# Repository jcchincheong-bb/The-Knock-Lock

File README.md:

# Knock Lock

<!-- <div id="logo" align="center">
<figure>
  
</figure>
</div> -->

As children, many of us might have invented secret knocks that we used to identify ourselves to our friends or siblings. But, what if those special codes could actually unlock the door itself? As adults, how many times have you forgotten your keys and wished you could just knock in a certain way and the door would unlock for you? As such, the aim of The Knock Lock project is to design and assemble a system that unlocks a door by recognising a specific knocking pattern. As a proof of concept, the system will be designed as a small lock box with the hope of extending the idea to work on a full door in the future.

This project was done as part of the course 2314 Practical Electronics at HSRW. The full project report can be found [here](https://github.com/AbhinavK02/Knock-Lock/blob/main/ProjectReport.md).

<div align="center">
  <table border="0" style="width: 100%; border: none;">
    <tr>
      <td align="left" style="vertical-align: middle; width: auto; padding: 10px 0;">
        by: <a href="https://abhinavk02.github.io/">Abhinav Kothari</a> and <a href="https://jcchincheong-bb.github.io/">Justin Chin Cheong</a>
      </td>
      <td align="right" style="vertical-align: middle; width: 1%; white-space: nowrap; padding-left: 20px;">
        
      </td>
    </tr>
  </table>
  </figure>

</div>

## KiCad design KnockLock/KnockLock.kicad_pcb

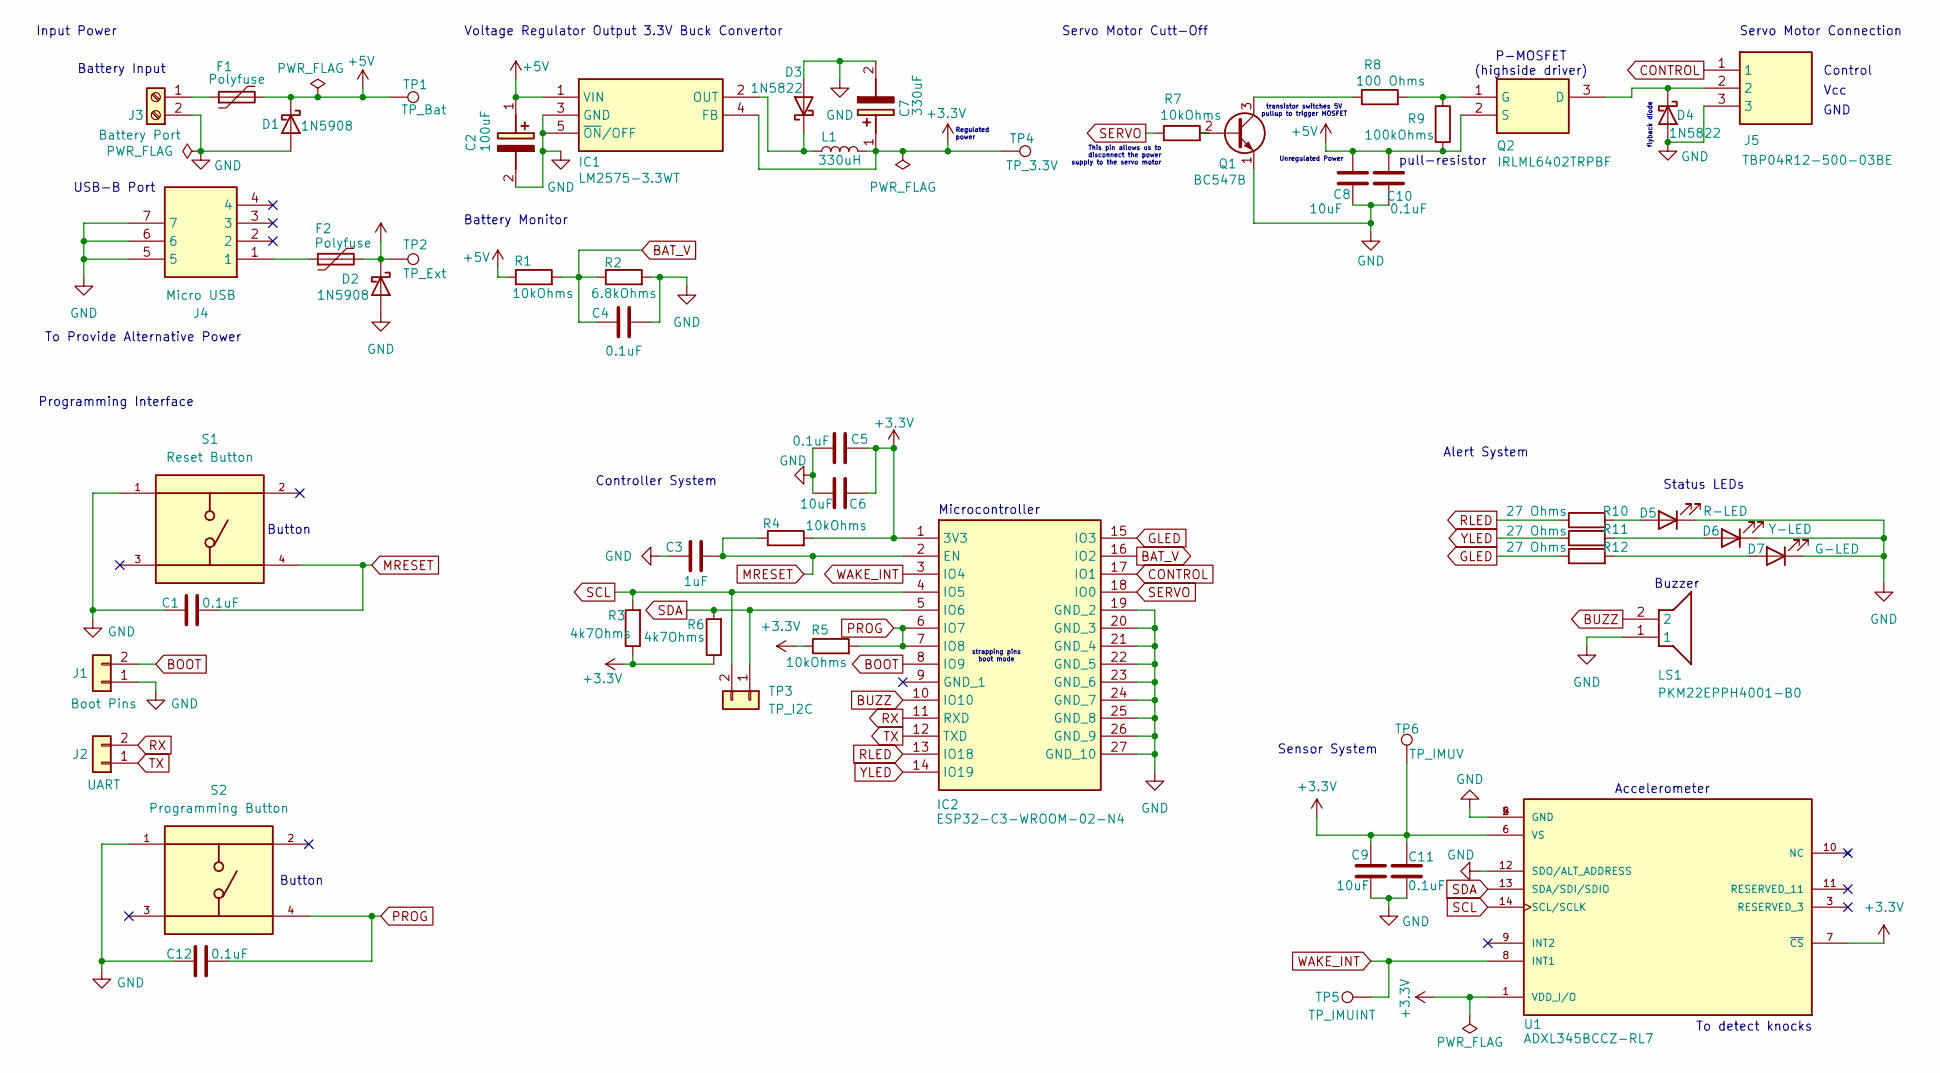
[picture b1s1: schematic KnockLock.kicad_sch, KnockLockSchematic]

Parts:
C1, C4, C5, C10, C11, C12: 0.1uF; C_0805_2012Metric_Pad1.18x1.45mm_HandSolder
C2: 100uF; CAPPRD250W55D630H1220; Mouser Part Number 667-EEU-FC1C101H
C3: 1uF; C_Radial_D4.0mm_H7.0mm_P1.50mm
C6, C8, C9: 10uF; C_Radial_D5.0mm_H11.0mm_P2.00mm
C7: 330uF; CAPPRD350W65D800H1300; Mouser Part Number 667-EEU-FR1E331
D1, D2: 1N5908; D_DO-201AD_P15.24mm_Horizontal
D3, D4: 1N5822; D_DO-201AD_P15.24mm_Horizontal
D5: R-LED; LED_D3.0mm
D6: Y-LED; LED_D3.0mm
D7: G-LED; LED_D3.0mm
F1, F2: Polyfuse; Fuse_BelFuse_0ZRE0012FF_L8.3mm_W3.8mm
IC1: LM2575-3.3WT; LM257533WT; Mouser Part Number 998-LM2575-3.3WT
IC2: ESP32-C3-WROOM-02-N4; ESP32C3WROOM02N4; Mouser Part Number 356-ESP32C3WROOM02N4
J1: Boot Pins; PinHeader_1x02_P2.54mm_Vertical
J2: UART; PinSocket_1x02_P2.54mm_Vertical
J3: Battery Port; TerminalBlock_bornier-2_P5.08mm
J4: Micro USB; USB3145301A; Mouser Part Number 640-USB3145-30-1-A
J5: TBP04R12-500-03BE; JST_EH_S3B-EH_1x03_P2.50mm_Horizontal; Mouser Part Number 179-TBP04R12-50003BE
L1: 330uH; L_Radial_D9.5mm_P5.00mm_Fastron_07HVP
LS1: PKM22EPPH4001-B0; PKM22EPPH4001B0; Mouser Part Number 81-PKM22EPPH4001-B0
Q1: BC547B; TO-92_HandSolder
Q2: IRLML6402TRPBF; SOT95P237X112-3N; Mouser Part Number 942-IRLML6402TRPBF
R1, R4, R5, R7: 10kOhms; R_1206_3216Metric_Pad1.30x1.75mm_HandSolder
R2: 6.8kOhms; R_1206_3216Metric_Pad1.30x1.75mm_HandSolder
R3, R6: 4k7Ohms; R_1206_3216Metric_Pad1.30x1.75mm_HandSolder
R8: 100 Ohms; R_1206_3216Metric_Pad1.30x1.75mm_HandSolder
R9: 100kOhms; R_1206_3216Metric_Pad1.30x1.75mm_HandSolder
R10, R11, R12: 27 Ohms; R_1206_3216Metric_Pad1.30x1.75mm_HandSolder
S1: Reset Button; SW_TS02-66-60-BK-260-LCR-D; PARTREV 1.0
S2: Programming Button; SW_TS02-66-60-BK-260-LCR-D; PARTREV 1.0
TP1: TP_Bat; TestPoint_Pad_D1.5mm
TP2: TP_Ext; TestPoint_Pad_D1.5mm
TP3: TP_I2C; PinSocket_1x02_P2.54mm_Vertical
TP4: TP_3.3V; TestPoint_Pad_D1.5mm
TP5: TP_IMUINT; PinSocket_1x01_P2.54mm_Vertical
TP6: TP_IMUV; TestPoint_Pad_D1.5mm
U1: ADXL345BCCZ-RL7; PQFN80P500X300X100-14N; PARTREV B

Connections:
+3.3V: C5.2, C6.2, C7.1 (+), C9.2, C11.2, IC1.4 (FB), IC2.1 (3V3), L1.2, R3.1, R4.2, R5.1, R6.1, TP4.1, TP6.1, U1.1 (VDD_I/O), U1.6 (VS), U1.7 (~CS)
+5V: C2.1 (+), C8.2, C10.2, D1.1 (K), D2.1 (K), F1.2, F2.2, IC1.1 (VIN), Q2.2 (S), R1.1, R9.2, TP1.1, TP2.1
BAT_V: C4.1, IC2.16 (IO2), R1.2, R2.1
BOOT: IC2.8 (IO9), J1.2
BUZZ: IC2.10 (IO10), LS1.2
CONTROL: IC2.17 (IO1), J5.1
GLED: IC2.15 (IO3), R12.1
GND: C1.1, C2.2 (-), C3.2, C4.2, C5.1, C6.1, C7.2 (-), C8.1, C9.1, C10.1, C11.1, C12.1, D1.2 (A), D2.2 (A), D3.2 (A), D4.2 (A), D5.1 (K), D6.1 (K), D7.1 (K), IC1.3 (GND), IC1.5 (~ON/OFF), IC2.19 (GND_2), IC2.20 (GND_3), IC2.21 (GND_4), IC2.22 (GND_5), IC2.23 (GND_6), IC2.24 (GND_7), IC2.25 (GND_8), IC2.26 (GND_9), IC2.27 (GND_10), J1.1, J3.2, J4.5, J4.6, J4.7, J5.3, LS1.1, Q1.1 (E), R2.2, S1.1, S2.1, U1.2 (GND), U1.4 (GND), U1.5 (GND), U1.12 (SDO/ALT_ADDRESS)
MRESET: C1.2, C3.1, IC2.2 (EN), R4.1, S1.4
unnamed: D3.1 (K), IC1.2 (OUT), L1.1
unnamed: D4.1 (K), J5.2, Q2.3 (D)
unnamed: D5.2 (A), R10.2
unnamed: D6.2 (A), R11.2
unnamed: D7.2 (A), R12.2
unnamed: F2.1, J4.1
unnamed: F1.1, J3.1
unnamed: Q1.2 (B), R7.2
unnamed: Q1.3 (C), R8.1
unnamed: Q2.1 (G), R8.2, R9.1
PROG: C12.2, IC2.6 (IO7), IC2.7 (IO8), R5.2, S2.4
RLED: IC2.13 (IO18), R10.1
RX: IC2.11 (RXD), J2.2
SCL: IC2.4 (IO5), R3.2, TP3.2, U1.14 (SCL/SCLK)
SDA: IC2.5 (IO6), R6.2, TP3.1, U1.13 (SDA/SDI/SDIO)
SERVO: IC2.18 (IO0), R7.1
TX: IC2.12 (TXD), J2.1
WAKE_INT: IC2.3 (IO4), TP5.1, U1.8 (INT1)
YLED: IC2.14 (IO19), R11.1

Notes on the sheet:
Voltage Regulator Output 3.3V Buck Convertor
Vcc
Battery Input
P-MOSFET (highside driver)
Controller System
To detect knocks
Control
Button
Programming Interface
flyback diode
strapping pins boot mode
Unregulated Power
Servo Motor Cutt-Off
Regulated power
Sensor System
GND
Buzzer
transistor switches 5V pullup to trigger MOSFET
Alert System
Servo Motor Connection
This pin allows us to disconnect the power supply to the servo motor
Input Power
Microcontroller
Accelerometer
Battery Monitor
Status LEDs
To Provide Alternative Power
USB-B Port
pull-resistor

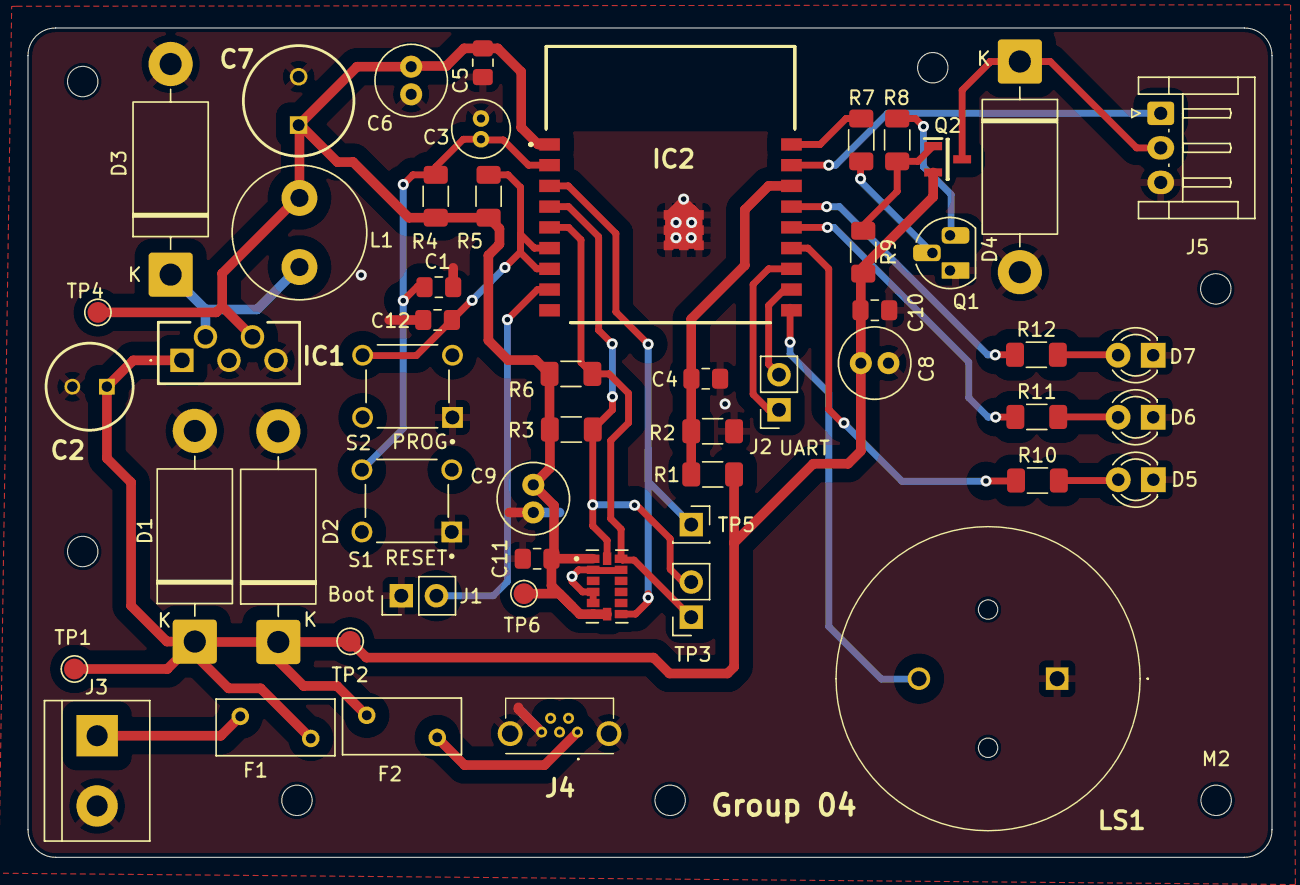
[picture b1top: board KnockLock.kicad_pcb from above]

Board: 2 copper layers, 90.0 x 60.0 mm, 55 parts (0 on the bottom side), 28 nets.

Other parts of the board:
M2, M2#2: MountingHole_2.2mm_M2_ISO7380

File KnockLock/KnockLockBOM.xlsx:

Item Number | Schematic Reference | Qty | Component | Part Number | Manufacturer | Vendor | Price Per Unit | Price
1 | U1 | 1 | Capacitive Accelerometer | ADXL345BCCZ-RL7 | Analog Devices | Mouser | 5.65 | 5.65 |  |  | Elect Cost | 26.61 | 15.05 | 11.56
2 | - | 1 | Servo Motor | SG90 | Soldered | HSRW | 5.07 | 5.07 |  |  | Mech Cost | 9.6999999999999993
3 | Q1 | 1 | Bipolar NPN Transistor | BC547B | CDIL | HSRW | 0.04 | 0.04 |  |  | PCB Cost | 7.24
4 | Q2 | 1 | P-channel MOSFET | IRLML6402TRPBF | Infineon Technologies | Mouser | 0.35 | 0.35 |  |  | Total Cost | 43.55
5 | IC2 | 1 | ESP32 Microcontroller | ESP32-C3-WROOM-02-N4 | Expressif Systems | Mouser | 3.12 | 3.12
6 | D5 | 1 | Red LED | DLE3MMR | Hottech | HSRW | 0.06 | 0.06
7 | D6 | 1 | Yellow LED | DLE3MMY | Hottech | HSRW | 0.06 | 0.06
8 | D7 | 1 | Green LED | DLE3MMG | Hottech | HSRW | 0.06 | 0.06
9 | LS1 | 1 | Buzzer | PKM22EPPH4001-B0 | Murata Electronics | Mouser | 0.48 | 0.48
10 | S1, S2 | 2 | Push Button | TS02-66-60-BK-260-LCR-D | Samesky | Mouser | 0.09 | 0.18
11 | IC1 | 1 | 3.3V Output Voltage Regulator | LM2575-3.3WT | Microchip Technology | Mouser | 1.48 | 1.48
12 | D1,D2 | 2 | TVS Diode | 1N5908 | STMicroelectronics | HSRW | 0.66 | 1.32
13 | D3,D4 | 2 | Schottky Diode | 1N5822 | MIC Electronics | HSRW | 0.15 | 0.3
14 | F1,F2 | 2 | Resettable Fuse | PFRA110 | Schurter | HSRW | 0.28000000000000003 | 0.56000000000000005
15 | - | 1 | Battery Holder | 2477 | Keystone Electronics | Mouser | 1.87 | 1.87
16 | - | 4 | AA Battery | - | - | HSRW | 0.3 | 1.2
17 | L1 | 1 | 330uH Inductor | RFC0810B-334KE | Coilcraft | Mouser | 1.26 | 1.26
18 | C1,C4,C5,C10,C11,C12 | 6 | 0.1uF Ceramic Capacitor SMT (0805) | B37873U5101S | EPCOS | HSRW | 0.11 | 0.66
19 | C2 | 1 | 100uF Electrolytic Capacitor | EEU-FC1C101H | Panasonic | HSRW | 0.14000000000000001 | 0.14000000000000001
20 | C3 | 1 | 1uF Electrolytic Capacitor | RA1/25-R | Jameco | HSRW | 0.02 | 0.02
21 | C6,C8,C9 | 3 | 10uF Electrolytic Capacitor | EEU-FR1H100 | Panasonic | HSRW | 0.11 | 0.33
22 | C7 | 1 | 330uF Electrolytic Capacitor | EEU-FR1E331 | Panasonic | HSRW | 0.26 | 0.26
23 | J1 | 1 | Male 2 Pin Header | - | - | HSRW | 0.08 | 0.08
24 | J2 | 1 | Female 2 Pin Header | - | - | HSRW | 0.1 | 0.1
25 | J3 | 1 | Male JST 2 Pin Header | - | - | HSRW | 0.1 | 0.1
26 | J4 | 1 | Micro USB B | USB3145-30-1-A | GCT | Mouser | 0.66 | 0.66
27 | J5 | 1 | Male JST 3 Pin Header | - | - | HSRW | 0.12 | 0.12
28 | R1,R4,R5,R7 | 4 | 10kOhms | RC1206FR-0710KL | YAGEO | HSRW | 0.09 | 0.36
29 | R2 | 1 | 6.8kOhms | RC1206FR-076K8L | YAGEO | HSRW | 0.09 | 0.09
30 | R3,R6 | 2 | 4k7Ohms | RC1206FR-074K7L | YAGEO | HSRW | 0.09 | 0.18
31 | R8 | 1 | 100 Ohms | RC1206FR-07100RL | YAGEO | HSRW | 0.09 | 0.09
32 | R9 | 1 | 100kOhms | RC1206FR-07100KL | YAGEO | HSRW | 0.09 | 0.09
33 | R10,R11,R12 | 3 | 27 Ohms | RC1206FR-0727RL | YAGEO | HSRW | 0.09 | 0.27
Item Number |  | Qty | Component | Price Per Unit | Price
35 |  | 7 | M2x6 Screw | 0.11 | 0.77
36 |  | 2 | M2x20 Screw | 0.14000000000000001 | 0.28000000000000003
37 |  | 1 | M3x15 Plastic Screw | 0.08 | 0.08
38 |  | 7 | M3 Plastic Washer | 0.01 | 7.0000000000000007E-2
39 |  | 1 | M3 Hex Nut | 7.0000000000000007E-2 | 7.0000000000000007E-2
40 |  | 1 | 3D Printed Housing | 8.43 | 8.43

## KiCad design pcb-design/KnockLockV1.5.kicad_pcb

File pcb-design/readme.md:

This is the folder where you save your pcb design with their related files. 

Please also submit a pdf / image version of your design

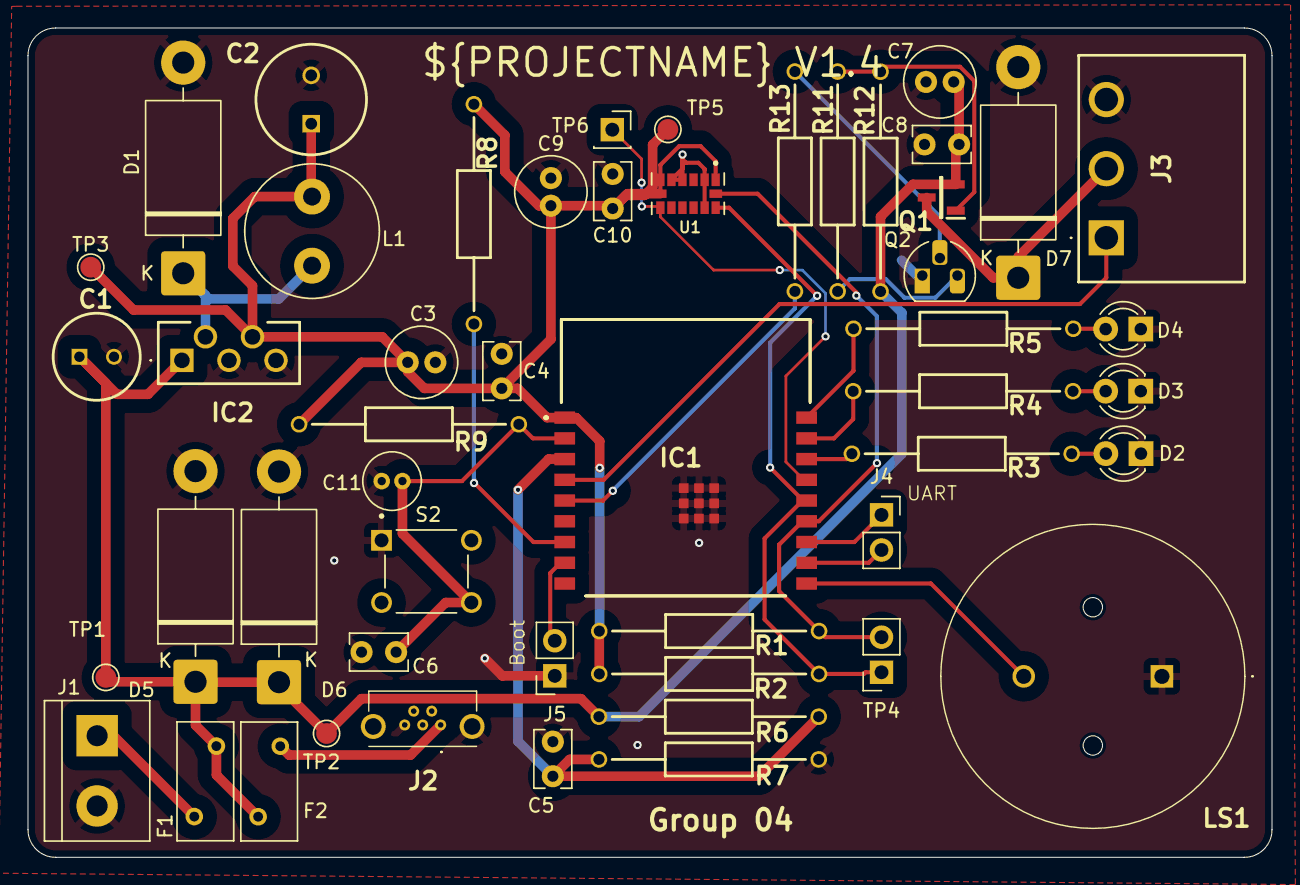
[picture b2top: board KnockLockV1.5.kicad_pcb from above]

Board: 2 copper layers, 90.0 x 60.0 mm, 51 parts (0 on the bottom side), 28 nets.

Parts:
C1: 100uF; CAPPRD250W55D630H1220
C2: 330uF; CAPPRD350W65D800H1300
C3, C7, C9: 10uF; C_Radial_D5.0mm_H11.0mm_P2.00mm
C4, C5, C6, C8, C10: 0.1uF; C_Rect_L4.0mm_W2.5mm_P2.50mm
C11: 1uF; C_Radial_D4.0mm_H7.0mm_P1.50mm
D1, D5, D6, D7: 1N5822; D_DO-201AD_P15.24mm_Horizontal
D2: R-LED; LED_D3.0mm
D3: Y-LED; LED_D3.0mm
D4: G-LED; LED_D3.0mm
F1, F2: Polyfuse; Fuse_BelFuse_0ZRE0012FF_L8.3mm_W3.8mm
IC1: ESP32-C3-WROOM-02-N4; ESP32C3WROOM02N4
IC2: LM2575-3.3WT; LM257533WT
J1: Screw_Terminal_01x02; TerminalBlock_bornier-2_P5.08mm
J2: USB3145-30-1-A; USB3145301A
J3: TBP04R12-500-03BE; TBP04R1250003BE
J4: UART; PinSocket_1x02_P2.54mm_Vertical
J5: Boot Pins; PinSocket_1x02_P2.54mm_Vertical
L1: 330uH; L_Radial_D9.5mm_P5.00mm_Fastron_07HVP
LS1: PKM22EPPH4001-B0; PKM22EPPH4001B0
Q1: IRLML6402TRPBF; SOT95P237X112-3N
Q2: BC547B; TO-92_HandSolder
R1, R2: 4k7Ohms; RESAD1590W60L630D240
R3, R4, R5: 27 Ohms; RESAD1590W60L630D240
R6, R8, R9, R13: 10kOhms; RESAD1590W60L630D240
R7: 6.8kOhms; RESAD1590W60L630D240
R11: 100 Ohms; RESAD1590W60L630D240
R12: 100kOhms; RESAD1590W60L630D240
S2: TS02-66-60-BK-260-LCR-D; SW_TS02-66-60-BK-260-LCR-D
TP1: TP_Bat; TestPoint_Pad_D1.5mm
TP2: TP_Ext; TestPoint_Pad_D1.5mm
TP3: TP_3.3V; TestPoint_Pad_D1.5mm
TP4: TP_I2C; PinSocket_1x02_P2.54mm_Vertical
TP5: TP_IMUV; TestPoint_Pad_D1.5mm
TP6: TP_IMUINT; PinSocket_1x01_P2.54mm_Vertical
U1: ADXL345BCCZ-RL7; PQFN80P500X300X100-14N

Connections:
+3.3V: C2.1 (+), C3.2, C4.2, C9.2, C10.2, IC1.1 (3V3), IC2.4 (FB), L1.2, R1.1, R2.1, R8.1, R9.2, TP3.1, TP5.1, U1.1 (VDD_I/O), U1.6 (VS), U1.7 (~CS)
+5V: C1.1 (+), C7.2, C8.2, D5.1 (K), D6.1 (K), F1.2, F2.2, IC2.1 (VIN), Q1.2 (S), R6.1, R12.2, TP1.1, TP2.1
BAT_V: C5.1, IC1.3 (IO4), R6.2, R7.1
BOOT: IC1.8 (IO9), J5.2
BUZZ: IC1.10 (IO10), LS1.2
CONTROL: IC1.4 (IO5), J3.1
GLED: IC1.18 (IO0), R5.1
GND: C1.2 (-), C2.2 (-), C3.1, C4.1, C5.2, C6.1, C7.1, C8.1, C9.1, C10.1, C11.2, D1.2 (A), D2.1 (K), D3.1 (K), D4.1 (K), D5.2 (A), D6.2 (A), D7.2 (A), IC1.19 (GND_2), IC1.20 (GND_3), IC1.21 (GND_4), IC1.22 (GND_5), IC1.23 (GND_6), IC1.24 (GND_7), IC1.25 (GND_8), IC1.26 (GND_9), IC1.27 (GND_10), IC2.3 (GND), IC2.5 (~ON/OFF), J1.2, J2.5, J2.6, J2.7, J3.3, J5.1, LS1.1, Q2.1 (E), R7.2, S2.1, U1.2 (GND), U1.4 (GND), U1.5 (GND), U1.12 (SDO/ALT_ADDRESS)
MRESET: C6.2, C11.1, IC1.2 (EN), R9.1, S2.4
unnamed: D1.1 (K), IC2.2 (OUT), L1.1
unnamed: D2.2 (A), R3.2
unnamed: D3.2 (A), R4.2
unnamed: D4.2 (A), R5.2
unnamed: D7.1 (K), J3.2, Q1.3 (D)
unnamed: F2.1, J2.1
unnamed: IC1.7 (IO8), R8.2
unnamed: F1.1, J1.1
unnamed: Q1.1 (G), R11.2, R12.1
unnamed: Q2.2 (B), R13.2
unnamed: Q2.3 (C), R11.1
RLED: IC1.16 (IO2), R3.1
RX: IC1.11 (RXD), J4.2
SCL: IC1.13 (IO18), R1.2, TP4.2, U1.14 (SCL/SCLK)
SDA: IC1.14 (IO19), R2.2, TP4.1, U1.13 (SDA/SDI/SDIO)
SERVO: IC1.5 (IO6), R13.1
TX: IC1.12 (TXD), J4.1
WAKE_INT: IC1.15 (IO3), TP6.1, U1.8 (INT1)
YLED: IC1.17 (IO1), R4.1

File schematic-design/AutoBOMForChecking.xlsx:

Reference | Qty | Value | DNP | Exclude from BOM | Exclude from Board | Footprint | Datasheet | Source | In Partslist
C1 | 1 | 100uF |  |  |  | SamacSys_Parts:CAPPRD250W55D630H1220 | http://industrial.panasonic.com/cdbs/www-data/pdf/RDF0000/AB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
C2 | 1 | 330uF |  |  |  | SamacSys_Parts:CAPPRD350W65D800H1300 | http://industrial.panasonic.com/cdbs/www-data/pdf/RDF0000/AB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
C3,C7,C9 | 3 | 10uF |  |  |  | Capacitor_THT:C_Radial_D5.0mm_H11.0mm_P2.00mm | ~
C4,C5,C6,C8,C10 | 5 | 0.1uF |  |  |  | Capacitor_THT:C_Rect_L4.0mm_W2.5mm_P2.50mm | ~ | Mouser | Y
C11 | 1 | 1uF |  |  |  | Capacitor_THT:C_Radial_D4.0mm_H7.0mm_P1.50mm | ~
D1,D5,D6,D7 | 4 | 1N5822 |  |  |  | Diode_THT:D_DO-201AD_P15.24mm_Horizontal | http://www.vishay.com/docs/88525/1n5817.pdf,http://www.vishay.com/docs/88526/1n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 | Reichelt | Y
D2 | 1 | R-LED |  |  |  | LED_THT:LED_D3.0mm | ~ | HSRW | Y
D3 | 1 | Y-LED |  |  |  | LED_THT:LED_D3.0mm | ~ | HSRW | Y
D4 | 1 | G-LED |  |  |  | LED_THT:LED_D3.0mm | ~ | HSRW | Y
F1,F2 | 2 | Polyfuse |  |  |  | Fuse:Fuse_BelFuse_0ZRE0012FF_L8.3mm_W3.8mm | ~ | HSRW | Y
IC1 | 1 | ESP32-C3-WROOM-02-N4 |  |  |  | SamacSys_Parts:ESP32C3WROOM02N4 | https://www.mouser.ch/datasheet/2/891/Espressif_ESP32_C3_WRO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
IC2 | 1 | LM2575-3.3WT |  |  |  | SamacSys_Parts:LM257533WT | https://ww1.microchip.com/downloads/en/DeviceDoc/lm2575.pdf | Mouser | Y
J1 | 1 | Screw_Terminal_01x02 |  |  |  | TerminalBlock:TerminalBlock_bornier-2_P5.08mm | ~
J2 | 1 | USB3145-30-1-A |  |  |  | SamacSys_Parts:USB3145301A | https://gct.co/connector/usb3145 | Mouser | Y
J3 | 1 | TBP04R12-500-03BE |  |  |  | SamacSys_Parts:TBP04R1250003BE | https://www.sameskydevices.com/product/resource/tbp04r12-500.pdf
J4 | 1 | UART |  |  |  | Connector_PinHeader_2.54mm:PinHeader_1x02_P2.54mm_Vertical | ~
J5 | 1 | Boot Pins |  |  |  | Connector_PinHeader_2.54mm:PinHeader_1x02_P2.54mm_Vertical | ~
L1 | 1 | 330uH |  |  |  | Inductor_THT:L_Radial_D9.5mm_P5.00mm_Fastron_07HVP | ~ | Mouser | Y
LS1 | 1 | PKM22EPPH4001-B0 |  |  |  | SamacSys_Parts:PKM22EPPH4001B0 | https://www.murata.com/products/productdata/8801054064670/SP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
Q1 | 1 | IRLML6402TRPBF |  |  |  | SamacSys_Parts:SOT95P237X112-3N | http://www.infineon.com/dgdl/irlml6402pbf.pdf?fileId=5546d46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 | Mouser | Y
Q2 | 1 | BC547B |  |  |  | Package_TO_SOT_THT:TO-92_HandSolder | https://www.onsemi.com/pub/Collateral/2N3903-D.PDF
R1,R2 | 2 | 4k7Ohms |  |  |  | SamacSys_Parts:RESAD1590W60L630D240 | ~
R3,R4,R5 | 3 | 27 Ohms |  |  |  | SamacSys_Parts:RESAD1590W60L630D240 | ~
R6,R8,R9,R13 | 4 | 10kOhms |  |  |  | SamacSys_Parts:RESAD1590W60L630D240 | ~
R7 | 1 | 6.8kOhms |  |  |  | SamacSys_Parts:RESAD1590W60L630D240 | ~
R11 | 1 | 100 Ohms |  |  |  | SamacSys_Parts:RESAD1590W60L630D240 | ~
R12 | 1 | 100kOhms |  |  |  | SamacSys_Parts:RESAD1590W60L630D240 | ~
S2 | 1 | TS02-66-60-BK-260-LCR-D |  |  |  | TS02-66-60-BK-260-LCR-D:SW_TS02-66-60-BK-260-LCR-D |  | Mouser | Y
TP1 | 1 | TP_Bat |  |  |  | TestPoint:TestPoint_Pad_D1.5mm | ~
TP2 | 1 | TP_Ext |  |  |  | TestPoint:TestPoint_Pad_D1.5mm | ~
TP3 | 1 | TP_3V3 |  |  |  | TestPoint:TestPoint_Pad_D1.5mm | ~
TP4 | 1 | TP_I2C |  |  |  | Connector_PinHeader_2.54mm:PinHeader_1x02_P2.54mm_Vertical | ~
TP5 | 1 | TP_IMUV |  |  |  | TestPoint:TestPoint_Pad_D1.5mm | ~
TP6 | 1 | TP_IMUINT |  |  |  | Connector_PinSocket_2.54mm:PinSocket_1x01_P2.54mm_Vertical | ~
U1 | 1 | ADXL345BCCZ-RL7 |  |  |  | ADXL345BCCZ-RL7:PQFN80P500X300X100-14N |  | Mouser | Y

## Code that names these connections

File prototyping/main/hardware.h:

#ifndef HARDWARE_H
#define HARDWARE_H

#include <Arduino.h>       // Needed for Serial, digitalWrite, delay, HIGH/LOW
#include <Wire.h>
#include <Preferences.h>
#include <ESP32Servo.h>
#include <SparkFun_ADXL345.h>

extern Preferences prefs;

// Pins
extern const int SDA_PIN;
extern const int SCL_PIN;
extern const int SERVO_PIN;
extern const int BUZZER;
extern const int RLED;
extern const int YLED;
extern const int GLED;
extern const int BUTTON_PIN;

// Objects
extern ADXL345 adxl;
extern Preferences prefs;
extern Servo lockServo;

// Functions
void setupHardware();

#endif

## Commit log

2025-09-26 Update 9 files
    - /idea/Project-Description.md
    - /idea/Project-Idea.md
    - /pcb-design/readme.md
    - /presentation/.gitkeep
    - /presentation/readme.md
    - /resources/readme.md
2025-10-04 Ideas added
2025-10-07 Idea updated to only selected one
2025-10-11 Added project description with image
2025-10-11 Small change Project-Description.md
2025-10-11 Small formatting amendments
2025-10-11 Small amendments to Project-Description.md
2025-10-11 Upload New File
2025-10-11 Separating md Files
2025-10-11 Minor style adjustments in Project Desc.
2025-10-11 adjusting image size
2025-10-12 Editing Project Description pdf
2025-10-15 Added prototype testing code and video
2025-10-15 Amended project idea features
2025-10-22 IMU Testing + Prelim Partslist
2025-10-24 Added ECAD for ADXL345
2025-10-25 Schematic first draft, added datasheets, added partlist2 with some new components
2025-10-25 Organizing folders, added pcb (not done) and sch (first draft)
2025-10-25 version 1 for backup
2025-10-25 Reorganising KiCAD + Libraries
2025-10-25 Schematic Clean up
2025-10-25 Minor Adjustments + Footprints
2025-10-26 Backup of SchV1.1
2025-10-26 v1.3 of schematic with servo motor connection
2025-10-26 Fixed power gating
2025-10-26 added NPN to BOM
2025-10-26 Updated diode for safety margin, added diodes and servo to Partslist_Group_PE04_2.xlsx
2025-10-29 Removed old parts folder
2025-10-29 Some pcb refinement
2025-10-29 Reorganized schematic, added NPN for reset
2025-10-29 Shifting to USB port, so added port and UART, but UART not connected
2025-10-30 Started Programming Interface
    - we need to be careful with the IO pin logic so we can use basic buttons to enter programming mode or if we should try to use transistors (maybe also use the other side of the D flip flop)
2025-10-30 Reorganized, fixed pwr flags
2025-10-31 Schematic Prog
    - added buttons for programming interface
    - in V2 i removed flip flop for deep sleep mode operation
2025-10-31 Minor Update to V1.5
    - added RC delay for reset button
2025-10-31 clean up partslist
2025-11-02 Sch V2.1
    ### Programming Interface
    - Added pull up for the EN pin so it normmaly high
    - Switched the push button for the boot to pin headers for a jumper
    ### Power Safety
    - Added some decoupling capacitors to the end of the voltage regulator
    - added a fuse PFRA 110 (used 0ZRE0012FF footprint cause close enough)
2025-11-02 V2.1 adjustments
    - added all footprints
    - added all components to BOM
2025-11-03 Some minor changes - removed 2nd set of decoupling capacitors after voltage regulator, formatting
2025-11-03 Added back decoupling capacitors
2025-11-03 Fixed footprint for Piezo
2025-11-04 Changed USB port for vertical mount
2025-11-05 Made first draft of pcb design, modified existing library symbol, changes to BOM, changes to schematic
2025-11-05 Minor adjustments to PCB design, fixed DRCs
2025-11-05 Edited schematic to have uart directly
2025-11-06 Started routing
2025-11-06 return to direct uart
2025-11-06 First draft of routing complete, parts list updated, 3d models added, button changed
2025-11-06 Created back up of versions
2025-11-07 Arduino Bridge Sketch
2025-11-07 Updates to PCB Dft
    - I added some labels on the silkscreen for the boot and UART pins
    - Cleaned up the voltage regulator circuit
    - Made sure everything connets to the ground plane
    - added some GND vias
2025-11-08 Plotted pdf, changed to female pin headers, minor tweaks
2025-11-08 PCB Net Fixes
    - made the ground planes more connected for better dissipation and flow
    - fixed an error where we had a 3V3 net and 3.3V net, switched to 3.3V net so everything is now properly connected
2025-11-08 Updates to datasheet names
2025-11-08 Re annotated for sequential passives names
2025-11-09 Minor Updates and Export of 3D Model Pics
2025-11-11 Added Logo options
2025-11-12 Updating Footprints
2025-11-12 pcb w/o sch changes
2025-11-12 Major Updates
    - moving the ESP32 to the edge with a keep out zone
    - adding a button for a programming mode
    - changing resistors and 0.1uF capacitors to SMT
    - increasing signal track sizes from 0.3 to 0.5
    - re-routing to accomodate better decoupling
2025-11-12 Conflict Fix
2025-11-12 Ensuring Proper Clearance Setttings
2025-11-12 Minor Updates to 3D models
2025-11-13 PCB Final Touches
    - added the logo
    - added mounting holes
    - double checked DRC against AISLER reqs
2025-11-13 updating the BOM
2025-11-14 KnockDetection and PatternRecording codes
2025-11-15 Thermal Adjustments
    - added some additional vias to the heat sink of the MCU for better thermal relief into the button ground plane
2025-11-16 Updates to 3D Model
    - I made sure each component has a 3D model
    - I changed the JST connector to the one the Lab has
2025-11-17 First Draft of Housing
    - created a basic safe
    - created a door with mounting holes, space for LED diffusion and built in button
    - still need to do the hinge pins + slot for servo latch
2025-11-17 Fixed many DRC errors, updated power supply connection to a JST 2.50mm
2025-11-18 Added holes for LEDs and Piezo for louder sound
2025-11-18 fixing final ERC errors
2025-11-19 Final uploaded PCB design
2025-11-24 Made code modular, added a lot of features
2025-11-26 Updating the 3D Model for final PCB
2025-11-27 collection of parts in spreadsheet
2025-12-04 KL backup
2025-12-04 Added Hinge.SLDPRT
2025-12-04 Housing w/ Latch Holes
2025-12-05 3D Printing
2025-12-10 TryingToMergeCodes
2025-12-10 Minor tweaks
2025-12-10 Pins updated
2025-12-18 3D Model updated, and code
2025-12-18 Minor modification to Button press
2025-12-19 Fixes
2025-12-19 Working version - remember
2025-12-26 Started making modular and a little bit of documentation
2025-12-29 Make modular, added configs etc
2025-12-30 Made a new hopefully better version of main code, with a different aDynamic calc and some minor changes. Also completed the literature revew and started methodology on SW
2025-12-30 Small naming change
2025-12-30 Minor change
2026-01-04 Changes to code, sleep mode improvements, documented more code, and literature review updated, included our initial prototyping
2026-01-04 Images editted
2026-01-04 Minor tweak
2026-01-05 Some more changes
2026-01-05 Model updates
2026-01-05 Model changes and print model
2026-01-06 Model changes
2026-01-07 Code fixed, no allowed mistakes anymore
2026-01-08 fixes to 3D model
2026-01-09 Fixed mistake tolerance, added better comments, fixed button model
2026-01-10 Rework of report structure
    I tried to make the report as scientific as possible while also following the development process
    I used the V model to do basic structuring
2026-01-10 Comment improvements, more documentation, SW documentation complete
2026-01-10 SW Documentation Compelte
2026-01-12 Small fix to values
2026-01-13 restructured again
2026-01-14 Presentation done, first draft, 3d model, reading style changed
2026-01-14 Added Logo
    also testing captions
2026-01-14 Testing figure captions and references
2026-01-14 Forgot to change image path
2026-01-14 testing references and captions
2026-01-14 Logo and removing tests
2026-01-14 testing pandoc with Docker
2026-01-14 Fixed config, images organized, ppt updated, excel sheet for feedbacks
2026-01-14 Fixed for new folder format
2026-01-14 testing runner
2026-01-14 Push again to test pandoc runner
2026-01-15 short writing and pandoc disable
    I couldn't figure out how to get the runner to work so I am deleting the .yml file so that the runner doesn't keep taking the job and failing
2026-01-15 Delete .gitlab-ci.yml
    I couldn't figure out how to get the runner to work so I am deleting the .yml file so that the runner doesn't keep taking the job and failing
2026-01-15 Revert "Delete .gitlab-ci.yml"
    This reverts commit 24fa7d2112104584774491a5f2b36a68ef719a4d.
2026-01-15 Reapply "Delete .gitlab-ci.yml"
    This reverts commit e908faa1bd201c78399ee40da17978b2f78b83bc.
2026-01-15 Methdology Progress
    + images for schematics, theory and housing design
    + work distribution for writing
    * heading numbers and some figures
2026-01-15 minor fixes
2026-01-15 Sensor Testing and Selection done
2026-01-15 Presentation worked, images add
2026-01-15 small restructure + images
    * structure of methodology to combine schematics with component specifications. This way the schematic is better view as the specifications of the components is discussed
    + images of PCB layouts and final
2026-01-15 README Updates
2026-01-15 Almost done design
2026-01-15 More documentation lit review done, section 4 updated
2026-01-15 Numbering fixes
2026-01-15 Circuit Design is done
2026-01-15 Updating software design and implementation
2026-01-15 Another video
2026-01-16 Code desc updated
2026-01-16 image size fixes
2026-01-16 image resolution update
2026-01-16 Updating resolution of schematic
2026-01-16 description of pre-implementation verification testing
2026-01-17 Adding PCB design
2026-01-17 testing side by side images with <table>
2026-01-17 Another test for side by side images with captions
2026-01-17 Another side by side image test
    * equal height
    * no border
2026-01-17 Software implementation completed, formula add to section 4 for battery voltage
2026-01-17 Fixing math eq
2026-01-17 math fix
2026-01-17 verification and validation defined
    + all test specifications defined
    + More information for the BOM
    + completed all info for power consumption and battery life estimation
2026-01-17 minor image and math fixes
2026-01-17 pre-imp vefication done
2026-01-17 Software description done, Discussion done, Conclusion Done, BOM updated
2026-01-17 PCB module performance and sub-system integration results done
2026-01-17 fixing housing images
2026-01-17 Flowcharts updated, presentation updated, images added, older images folder deleted
2026-01-17 Unecessary datasheet removed
2026-01-17 verfication done
2026-01-17 update product showcase
2026-01-17 Product Show case instructions
2026-01-17 Video uploaded, link added
2026-01-17 Allignment fix
2026-01-17 user feedback
2026-01-17 some image changes
2026-01-17 Theory done
2026-01-17 Improved discussion, updated BOM
2026-01-17 Paragraph fixes
2026-01-17 Redid Introduction and appendices
2026-01-17 Minor fixes from merge
2026-01-17 updating figure and table numbers
2026-01-18 Deleting unncessary images
2026-01-18 removed unnecessary models
2026-01-18 Some minor tweaks, spacing, wording fixes, spelling fixes, lastly added user feedback into future improvements more clearly. Also added link to link references from all sources cited in text
2026-01-18 * reference links
2026-01-18 * reference links (again)
2026-01-18 + HSRW logo
2026-01-18 annotated images
2026-01-18 aesthetic changes
    + more transistion sentences
    - spelling issues
    + annotations to some images
    * fixed cost miscalculation
    + acknowledgement
    + abstract
2026-01-18 some stuff
2026-01-18 Fixing table
2026-01-18 fixing tables
2026-01-18 reducing size
2026-01-18 table fixes again
2026-01-18 Fixing logo
2026-01-18 size fix
2026-01-18 better merge fix
2026-01-18 minor fix
2026-01-18 + extra slides in reserve, * minor fixes
2026-01-18 spelling and grammar final fixes
2026-02-08 Model fixes for hinges
2026-03-02 LaTeX setup
2026-03-02 repo rebase
2026-03-02 Fixing image errors
2026-03-02 Removing images from lfs
2026-03-02 Track image files with Git LFS
2026-03-02 image reset
2026-03-02 re-add images
2026-03-02 temp image reset
